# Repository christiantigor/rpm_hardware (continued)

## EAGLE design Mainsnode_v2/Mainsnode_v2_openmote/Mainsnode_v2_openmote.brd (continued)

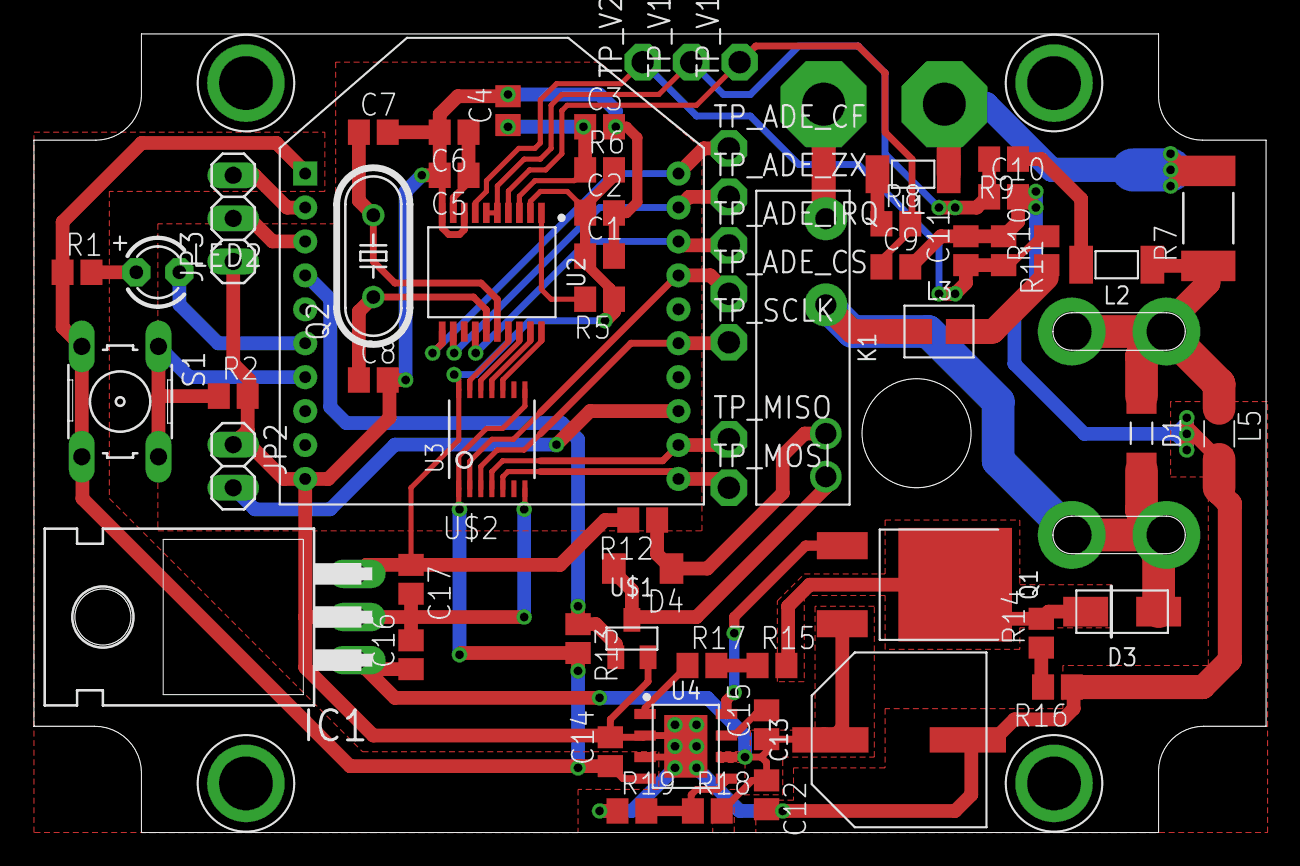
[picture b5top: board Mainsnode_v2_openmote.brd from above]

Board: 2 copper layers, 72.6 x 47.1 mm, 71 parts (0 on the bottom side), 46 nets.

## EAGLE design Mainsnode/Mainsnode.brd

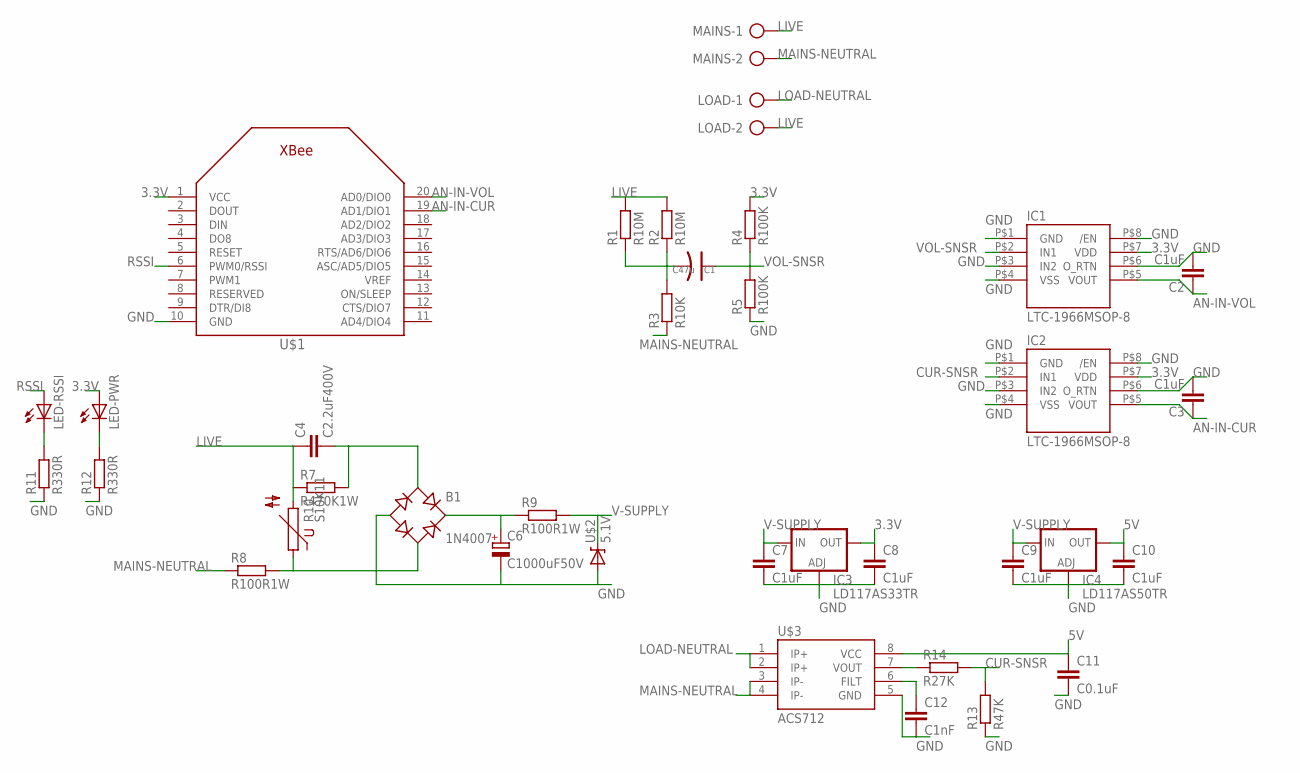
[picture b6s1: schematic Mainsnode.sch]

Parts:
B1: 1N4007; RB1A
C1: C47u; AVX-C
C2, C3, C7, C8, C9, C10: C1uF; C0805
C4: C2.2uF400V; C150-064X183
C6: C1000uF50V; E2-5
C11: C0.1uF; C0805
C12: C1nF; C0805
IC1, IC2: LTC-1966MSOP-8; MSOP-8
IC3: LD117AS33TR; SOT223
IC4: LD117AS50TR; SOT223
LED-PWR: LED0603; LED-0603
LED-RSSI: LED0603; LED-0603
LOAD: AK300/2
MAINS: AK300/2
R1: R10M; 0309V
R2: R10M; R0603
R3: R10K; R0603
R4, R5: R100K; R0603
R7: R470K1W; 0309V
R8, R9: R100R1W; 0309V
R10: S10K11
R11, R12: R330R; R0603
R13: R47K; R0603
R14: R27K; R0603
U$1: XBEE
U$2: 5.1V; DIODE-ZENER
U$3: ACS712; SO08

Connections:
3.3V: C8.1, IC1.P$7 (VDD), IC2.P$7 (VDD), IC3.4 (OUT), LED-PWR.A, R4.2, U$1.1 (VCC)
5V: C10.1, C11.1, IC4.4 (OUT), U$3.8 (VCC)
AN-IN-CUR: C3.1, IC2.P$5 (VOUT), U$1.19 (AD1/DIO1)
AN-IN-VOL: C2.1, IC1.P$5 (VOUT), U$1.20 (AD0/DIO0)
CUR-SNSR: IC2.P$2 (IN1), R13.2, R14.2
GND: B1.-, C2.2, C3.2, C6.-, C7.2, C8.2, C9.2, C10.2, C11.2, C12.2, IC1.P$1 (GND), IC1.P$3 (IN2), IC1.P$4 (VSS), IC1.P$6 (O_RTN), IC1.P$8 (/EN), IC2.P$1 (GND), IC2.P$3 (IN2), IC2.P$4 (VSS), IC2.P$6 (O_RTN), IC2.P$8 (/EN), IC3.1 (ADJ), IC4.1 (ADJ), R5.1, R11.1, R12.1, R13.1, U$1.10 (GND), U$2.P$2 (A), U$3.5 (GND)
LIVE: C4.1, LOAD.2, MAINS.1, R1.2, R2.2, R7.1, R10.2
LOAD-NEUTRAL: LOAD.1, U$3.1 (IP+), U$3.2 (IP+)
MAINS-NEUTRAL: MAINS.2, R3.1, R8.1, U$3.3 (IP-), U$3.4 (IP-)
unnamed: C1.- (2), R1.1, R2.1, R3.2
unnamed: B1.+, C6.+, R9.1
unnamed: LED-RSSI.C, R11.2
unnamed: B1.AC1, C4.2, R7.2
unnamed: B1.AC2, R8.2, R10.1
unnamed: C12.1, U$3.6 (FILT)
unnamed: LED-PWR.C, R12.2
unnamed: R14.1, U$3.7 (VOUT)
RSSI: LED-RSSI.A, U$1.6 (PWM0/RSSI)
V-SUPPLY: C7.1, C9.1, IC3.3 (IN), IC4.3 (IN), R9.2, U$2.P$1 (C)
VOL-SNSR: C1.+ (1), IC1.P$2 (IN1), R4.1, R5.2

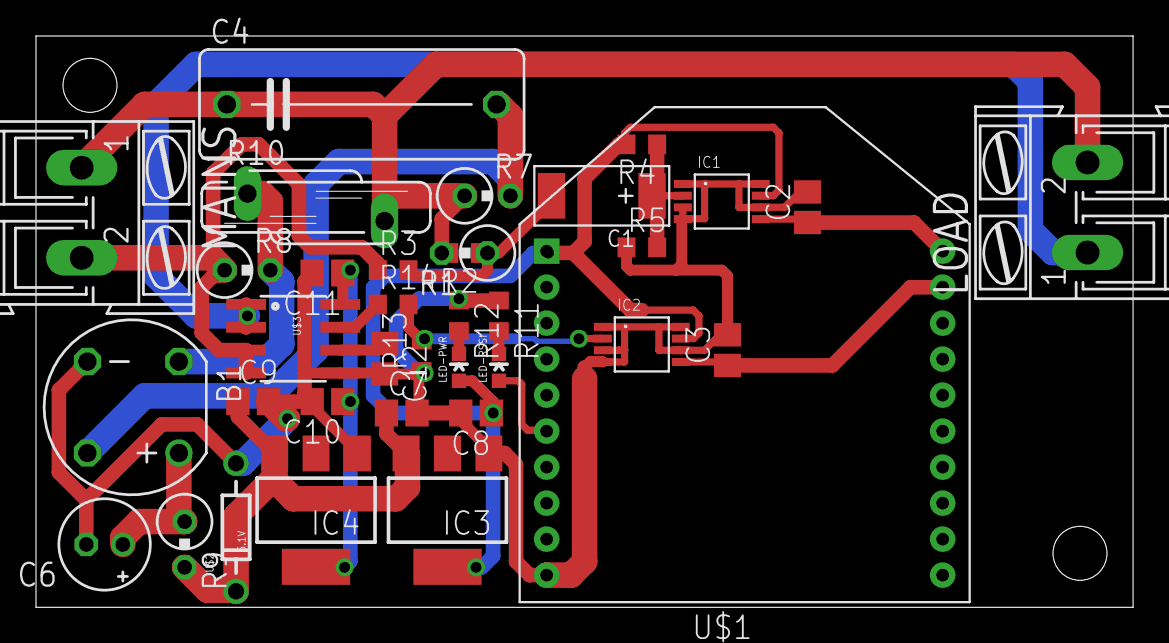
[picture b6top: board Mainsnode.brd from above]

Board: 2 copper layers, 60.9 x 31.7 mm, 36 parts (0 on the bottom side), 20 nets.

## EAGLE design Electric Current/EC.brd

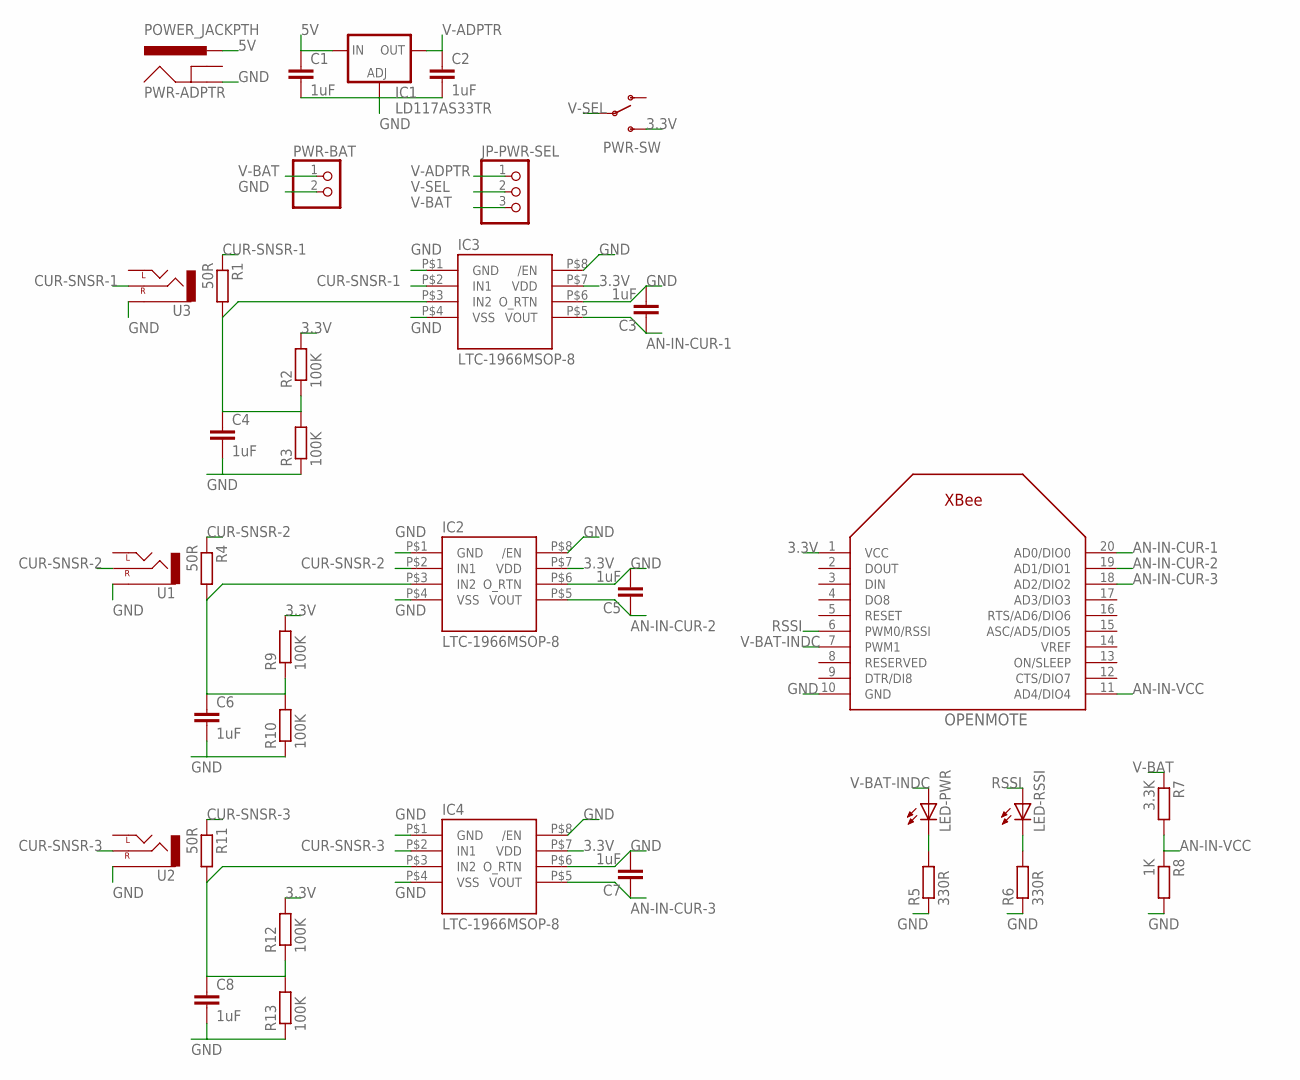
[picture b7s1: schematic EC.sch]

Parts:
C1, C2, C3, C4, C5, C6, C7, C8: 1uF; C0805
IC1: LD117AS33TR; SOT223
IC2, IC3, IC4: LTC-1966MSOP-8; MSOP-8
JP-PWR-SEL: PINHD-1X3; 1X03
LED-PWR: LED0603; LED-0603
LED-RSSI: LED0603; LED-0603
OPENMOTE: XBEE
PWR-ADPTR: POWER_JACKPTH; POWER_JACK_PTH
PWR-BAT: PINHD-1X2; 1X02
PWR-SW: SWITCH-SPDTSMD2; SWITCH-SPDT-SMD
R1, R4, R11: 50R; R0603
R2, R3, R9, R10, R12, R13: 100K; R0603
R5, R6: 330R; R0603
R7: 3.3K; R0603
R8: 1K; R0603
U1, U2, U3: AUDIO-JACKSMD2; AUDIO-JACK-3.5MM-SMD

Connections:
3.3V: IC2.P$7 (VDD), IC3.P$7 (VDD), IC4.P$7 (VDD), OPENMOTE.1 (VCC), PWR-SW.3 (S), R2.2, R9.2, R12.2
5V: C1.1, IC1.3 (IN), PWR-ADPTR.PWR
AN-IN-CUR-1: C3.1, IC3.P$5 (VOUT), OPENMOTE.20 (AD0/DIO0)
AN-IN-CUR-2: C5.1, IC2.P$5 (VOUT), OPENMOTE.19 (AD1/DIO1)
AN-IN-CUR-3: C7.1, IC4.P$5 (VOUT), OPENMOTE.18 (AD2/DIO2)
AN-IN-VCC: OPENMOTE.11 (AD4/DIO4), R7.2, R8.1
CUR-SNSR-1: IC3.P$2 (IN1), R1.1, U3.RING (RIGHT)
CUR-SNSR-2: IC2.P$2 (IN1), R4.1, U1.RING (RIGHT)
CUR-SNSR-3: IC4.P$2 (IN1), R11.1, U2.RING (RIGHT)
GND: C1.2, C2.2, C3.2, C4.2, C5.2, C6.2, C7.2, C8.2, IC1.1 (ADJ), IC2.P$1 (GND), IC2.P$4 (VSS), IC2.P$6 (O_RTN), IC2.P$8 (/EN), IC3.P$1 (GND), IC3.P$4 (VSS), IC3.P$6 (O_RTN), IC3.P$8 (/EN), IC4.P$1 (GND), IC4.P$4 (VSS), IC4.P$6 (O_RTN), IC4.P$8 (/EN), OPENMOTE.10 (GND), PWR-ADPTR.GND, PWR-BAT.2, R3.1, R5.1, R6.1, R8.2, R10.1, R13.1, U1.SLEEVE, U2.SLEEVE, U3.SLEEVE
unnamed: LED-PWR.C, R5.2
unnamed: LED-RSSI.C, R6.2
unnamed: C4.1, IC3.P$3 (IN2), R1.2, R2.1, R3.2
unnamed: C6.1, IC2.P$3 (IN2), R4.2, R9.1, R10.2
unnamed: C8.1, IC4.P$3 (IN2), R11.2, R12.1, R13.2
RSSI: LED-RSSI.A, OPENMOTE.6 (PWM0/RSSI)
V-ADPTR: C2.1, IC1.4 (OUT), JP-PWR-SEL.1
V-BAT: JP-PWR-SEL.3, PWR-BAT.1, R7.1
V-BAT-INDC: LED-PWR.A, OPENMOTE.7 (PWM1)
V-SEL: JP-PWR-SEL.2, PWR-SW.2

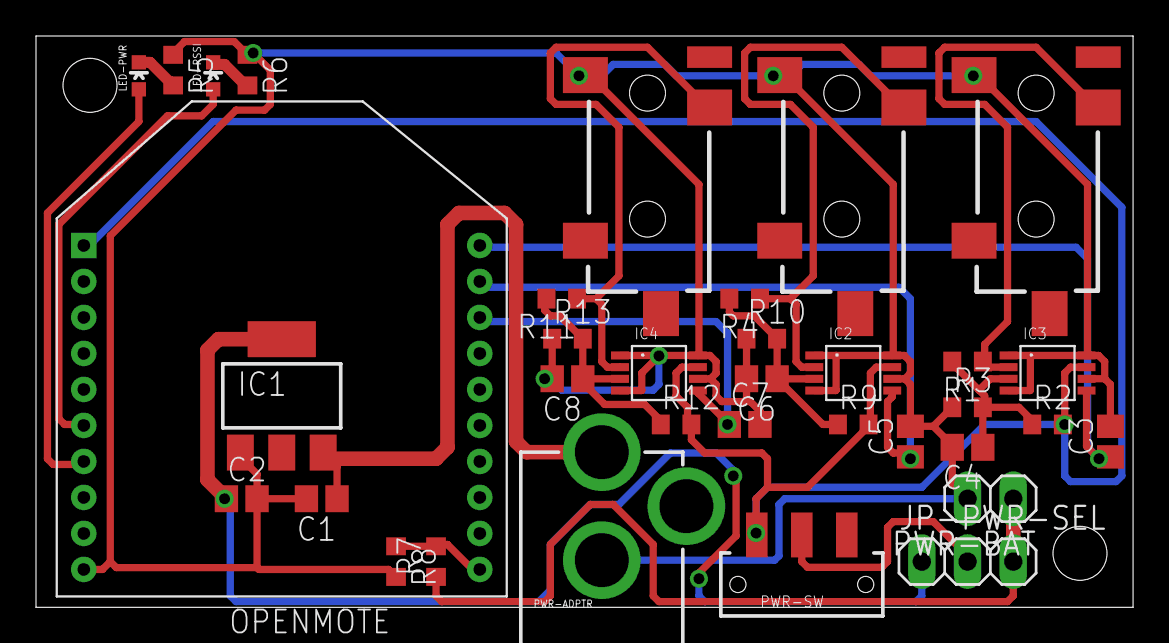
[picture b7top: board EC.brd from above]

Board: 2 copper layers, 60.9 x 31.7 mm, 35 parts (0 on the bottom side), 20 nets.

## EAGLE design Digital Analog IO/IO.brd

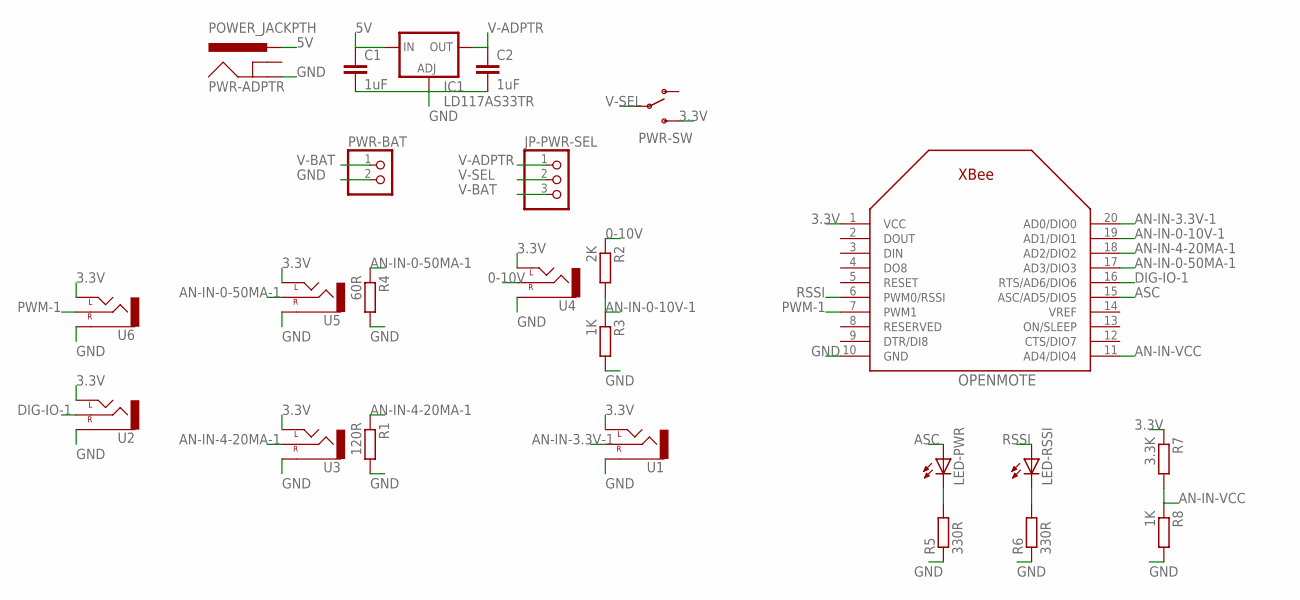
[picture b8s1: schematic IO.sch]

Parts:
C1, C2: 1uF; C0805
IC1: LD117AS33TR; SOT223
JP-PWR-SEL: PINHD-1X3; 1X03
LED-PWR: LED0603; LED-0603
LED-RSSI: LED0603; LED-0603
OPENMOTE: XBEE
PWR-ADPTR: POWER_JACKPTH; POWER_JACK_PTH
PWR-BAT: PINHD-1X2; 1X02
PWR-SW: SWITCH-SPDTSMD2; SWITCH-SPDT-SMD
R1: 120R; R0603
R2: 2K; R0603
R3, R8: 1K; R0603
R4: 60R; R0603
R5, R6: 330R; R0603
R7: 3.3K; R0603
U1, U2, U3, U4, U5, U6: AUDIO-JACKSMD2; AUDIO-JACK-3.5MM-SMD

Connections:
0-10V: R2.1, U4.RING (RIGHT)
3.3V: OPENMOTE.1 (VCC), PWR-SW.3 (S), R7.1, U1.TIP (LEFT), U2.TIP (LEFT), U3.TIP (LEFT), U4.TIP (LEFT), U5.TIP (LEFT), U6.TIP (LEFT)
5V: C1.1, IC1.3 (IN), PWR-ADPTR.PWR
AN-IN-0-10V-1: OPENMOTE.19 (AD1/DIO1), R2.2, R3.1
AN-IN-0-50MA-1: OPENMOTE.17 (AD3/DIO3), R4.1, U5.RING (RIGHT)
AN-IN-3.3V-1: OPENMOTE.20 (AD0/DIO0), U1.RING (RIGHT)
AN-IN-4-20MA-1: OPENMOTE.18 (AD2/DIO2), R1.1, U3.RING (RIGHT)
AN-IN-VCC: OPENMOTE.11 (AD4/DIO4), R7.2, R8.1
ASC: LED-PWR.A, OPENMOTE.15 (ASC/AD5/DIO5)
DIG-IO-1: OPENMOTE.16 (RTS/AD6/DIO6), U2.RING (RIGHT)
GND: C1.2, C2.2, IC1.1 (ADJ), OPENMOTE.10 (GND), PWR-ADPTR.GND, PWR-BAT.2, R1.2, R3.2, R4.2, R5.1, R6.1, R8.2, U1.SLEEVE, U2.SLEEVE, U3.SLEEVE, U4.SLEEVE, U5.SLEEVE, U6.SLEEVE
unnamed: LED-PWR.C, R5.2
unnamed: LED-RSSI.C, R6.2
PWM-1: OPENMOTE.7 (PWM1), U6.RING (RIGHT)
RSSI: LED-RSSI.A, OPENMOTE.6 (PWM0/RSSI)
V-ADPTR: C2.1, IC1.4 (OUT), JP-PWR-SEL.1
V-BAT: JP-PWR-SEL.3, PWR-BAT.1
V-SEL: JP-PWR-SEL.2, PWR-SW.2

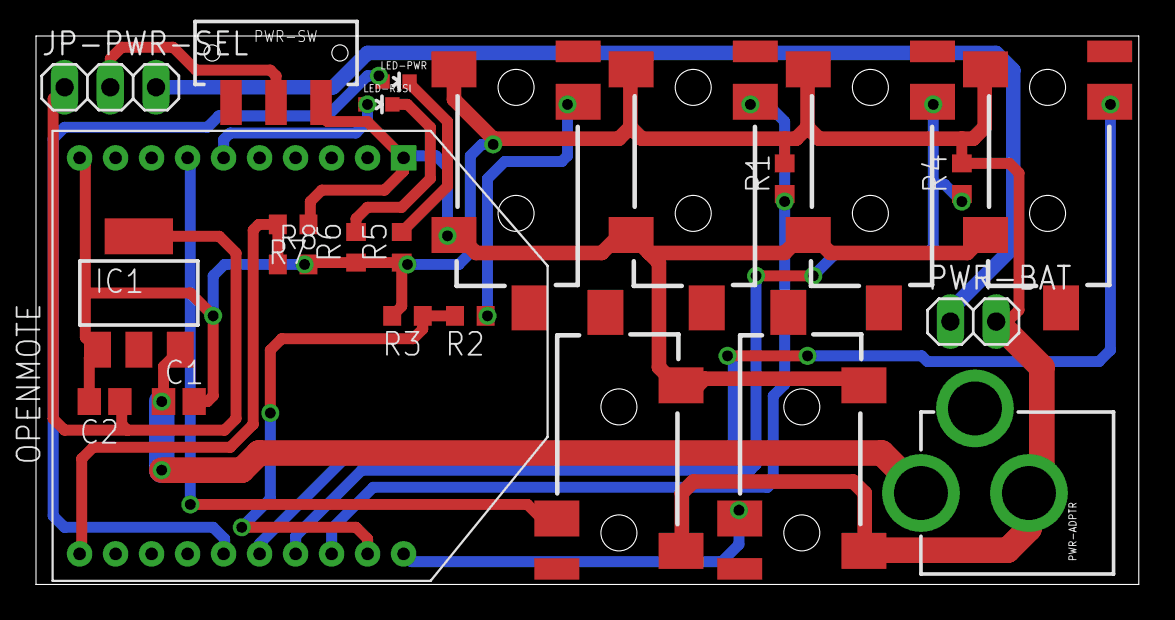
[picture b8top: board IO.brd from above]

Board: 2 copper layers, 61.3 x 30.5 mm, 24 parts (0 on the bottom side), 18 nets.

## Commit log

2014-07-14 :confetti_ball: Added .gitattributes & .gitignore files
2014-07-15 update PCB
2014-07-15 Electric current module
2014-07-17 3 phase meter, add spacer, reset LTC 1966 dim
2014-07-17 Initial commit of Mainsnode
2014-07-17 Update wire on EC module
2014-07-18 Add ACS712, 5V supply, conditioner 3.3V
2014-07-19 Add 0712 doc
2014-09-19 Add Mainsnode_v2
2014-09-23 Finish schematic, start PCB
2014-09-24 Change controller to openmote form factor
2014-09-25 Finish PCB Mainsnode_V2_openmote
    Ferrite bead DigiKey 240-2418 and 240-2520 and casing have not been
    ordered yet.
2014-09-29 Add Initial Casing Design
2014-09-30 Finish schematic wifi board
2014-10-01 Start route wifi board
2014-10-03 Finish route wifi board and order component
2014-11-28 add wifi board rev a
2014-11-28 updt wifi brd rev a (rmv cmpnents)
